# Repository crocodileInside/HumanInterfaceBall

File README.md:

# HumanInterfaceBall
A ball-shaped, BLE enabled human interface device using a **Bosch BNO055** IMU and a **Bosch BME280** environment sensor for mouse input control.  

## Hardware  
Using a RedBearLabs BLE Nano v2 (**nRF52832**) as MCU and for BLE communication.

## Software  
Written in Arduino, see Arduino folder

### Installation instructions  
In order to setup the required toolchain, follow these instructions:

1. Download and install [Arduino IDE](https://www.arduino.cc/en/Main/Software) >=1.6.12 (tested with 1.6.12)  
2. Install `arduino-nRF5` as described here: https://github.com/sandeepmistry/arduino-nRF5
3. Copy the contents of the `Arduino/libraries/` folder to your Arduino library folder (most likely at `Documents/Arduino/libraries`)
4. The default pin function mapping of our board in Arduino doesn't work with our PCB, so you need to replace your `variant.h` with the one provided in `Arduino/variant.h`  
The original variant.h is found at `C:\Users\<Username>\AppData\Local\Arduino15\packages\sandeepmistry\hardware\nRF5\0.4.0\variants\RedBear_BLENano2`
5. Plug in the DAPLink
6. Install the [mbed Serial Driver](https://os.mbed.com/handbook/Windows-serial-configuration)
7. Open the Arduino IDE (or restart, if it was open)
8. Choose *Tools -> Board -> RedBear BLE Nano 2*
9. Choose *Tools -> Softdevice -> S132*
10. Select the correct serial port for the DAPLink at *Tools -> Port* (sometimes displayed as *BBC:microBit*)
11. Choose *Tools -> Programmer -> CMSIS-DAP*
12. **factory new boards only**: Select *Tools -> nRF5 Flash SoftDevice* and wait for completion
13. Compile and flash the software using Arduino (or hit CTRL+U)
14. Finished!

*Created 01/2018 by C. Locher, M. Schuster, S. Oechslein, N. Rieth, T. Windberg*

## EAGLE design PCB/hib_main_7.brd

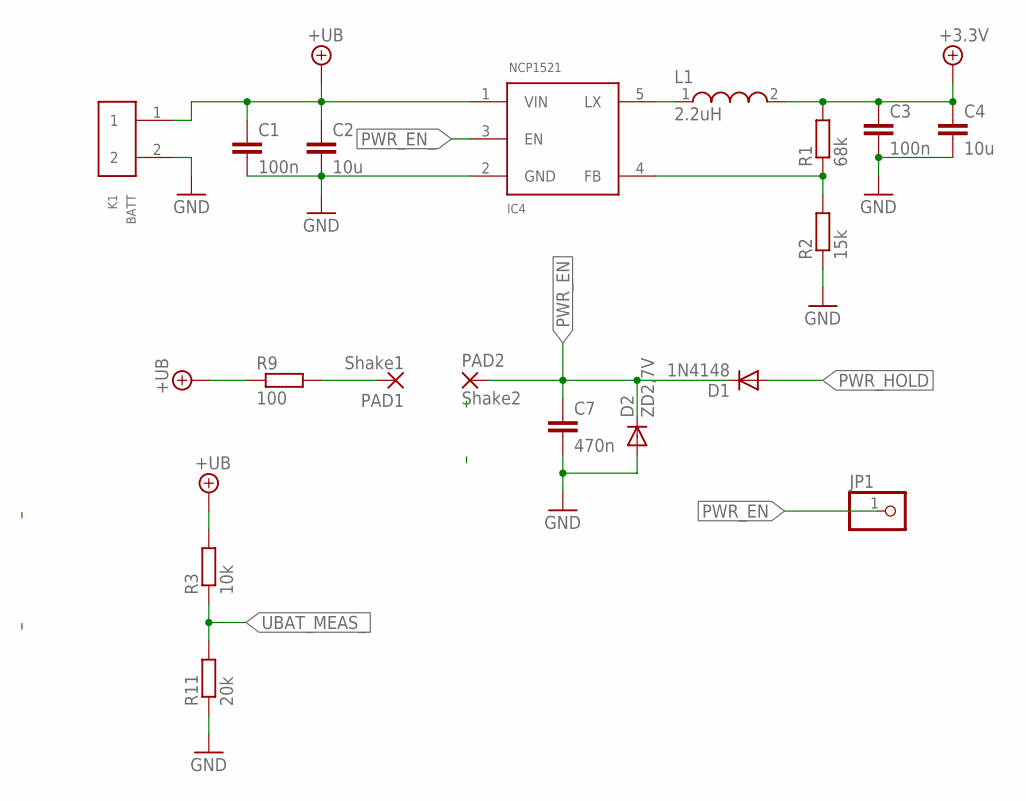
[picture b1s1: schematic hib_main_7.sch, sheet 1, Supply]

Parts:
C1: 100n; C0805K
C2: 10u; C0805K
C3: 100n; C0805M
C4: 10u; C0805M
C7: 470n; C0805M
D1: 1N4148; MINIMELF
D2: ZD2,7V; MINIMELF
IC4: NCP1521; SOT23-5L
JP1: PINHD-1X1; 1X01
K1: BATT; 620102131822
L1: 2.2uH; WE-MPSB_0805(W=4.0)
PAD1: Shake1; SMD1,27-2,54
PAD2: Shake2; SMD1,27-2,54
R1: 68k; R0603
R2: 15k; R0603
R3: 10k; R0603
R9: 100; R0603
R11: 20k; R0603

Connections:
+3,3V: C3.1, C4.1, L1.2, R1.2; also elsewhere on the board
+UB: C1.1, C2.1, IC4.1 (VIN), K1.1, R3.2, R9.1; also elsewhere on the board
GND: C1.2, C2.2, C3.2, C4.2, C7.2, D2.A, IC4.2 (GND), K1.2, R2.1, R11.1; also elsewhere on the board
unnamed: IC4.5 (LX), L1.1
unnamed: IC4.4 (FB), R1.1, R2.2
unnamed: PAD1.1, R9.2
PWR_EN: C7.1, D1.C, D2.C, JP1.1, PAD2.1
PWR_EN_: IC4.3 (EN); also elsewhere on the board
PWR_HOLD: D1.A; also elsewhere on the board
UBAT_MEAS_: R3.1, R11.2; also elsewhere on the board

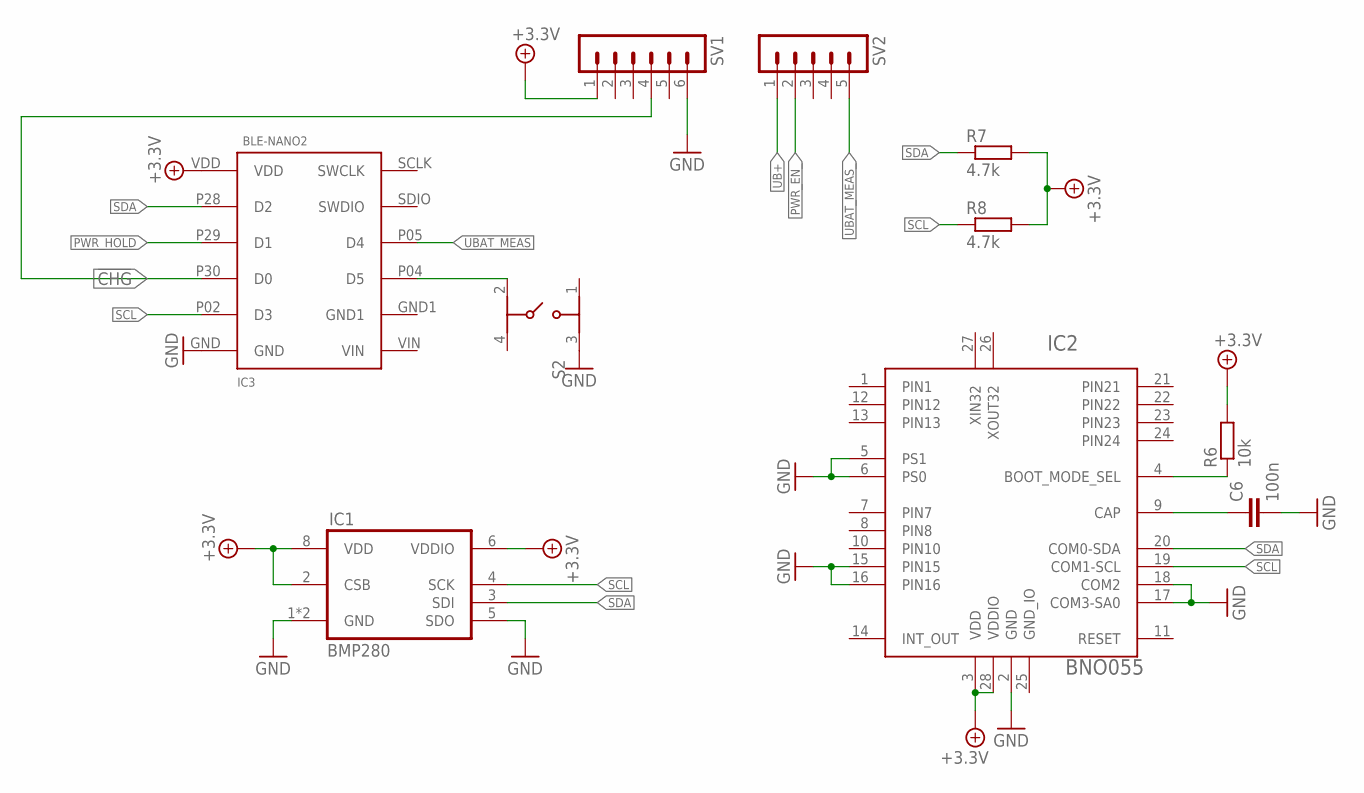
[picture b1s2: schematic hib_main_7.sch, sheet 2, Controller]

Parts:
C6: 100n; C0805M
IC1: BMP280
IC2: BNO055; LGA-28_3.80X5.20/0.5
IC3: BLE-NANO2
R6: 10k; R0805M
R7, R8: 4.7k; R0805M
S2: 434153017835
SV1: MA06-1
SV2: MA05-1

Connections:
!CHG!: IC3.P30 (D0), SV1.4; also elsewhere on the board
+3,3V: IC1.2 (CSB), IC1.6 (VDDIO), IC1.8 (VDD), IC2.3 (VDD), IC2.28 (VDDIO), IC3.VDD, R6.2, R7.2, R8.2, SV1.1; also elsewhere on the board
GND: C6.2, IC1.1 (GND), IC1.5 (SDO), IC1.7 (GND), IC2.2 (GND), IC2.5 (PS1), IC2.6 (PS0), IC2.15 (PIN15), IC2.16 (PIN16), IC2.17 (COM3-SA0), IC2.18 (COM2), IC3.GND, S2.3 (2), SV1.6; also elsewhere on the board
GND_IO: IC2.25 (GND_IO)
unnamed: C6.1, IC2.9 (CAP)
unnamed: IC2.4 (BOOT_MODE_SEL), R6.1
PWR_EN_: SV2.2; also elsewhere on the board
PWR_HOLD: IC3.P29 (D1); also elsewhere on the board
RESET: IC3.P04 (D5), S2.2 (3)
SCL: IC1.4 (SCK), IC2.19 (COM1-SCL), IC3.P02 (D3), R8.1
SDA: IC1.3 (SDI), IC2.20 (COM0-SDA), IC3.P28 (D2), R7.1
UB+: SV2.1
UBAT_MEAS: IC3.P05 (D4)
UBAT_MEAS_: SV2.5; also elsewhere on the board

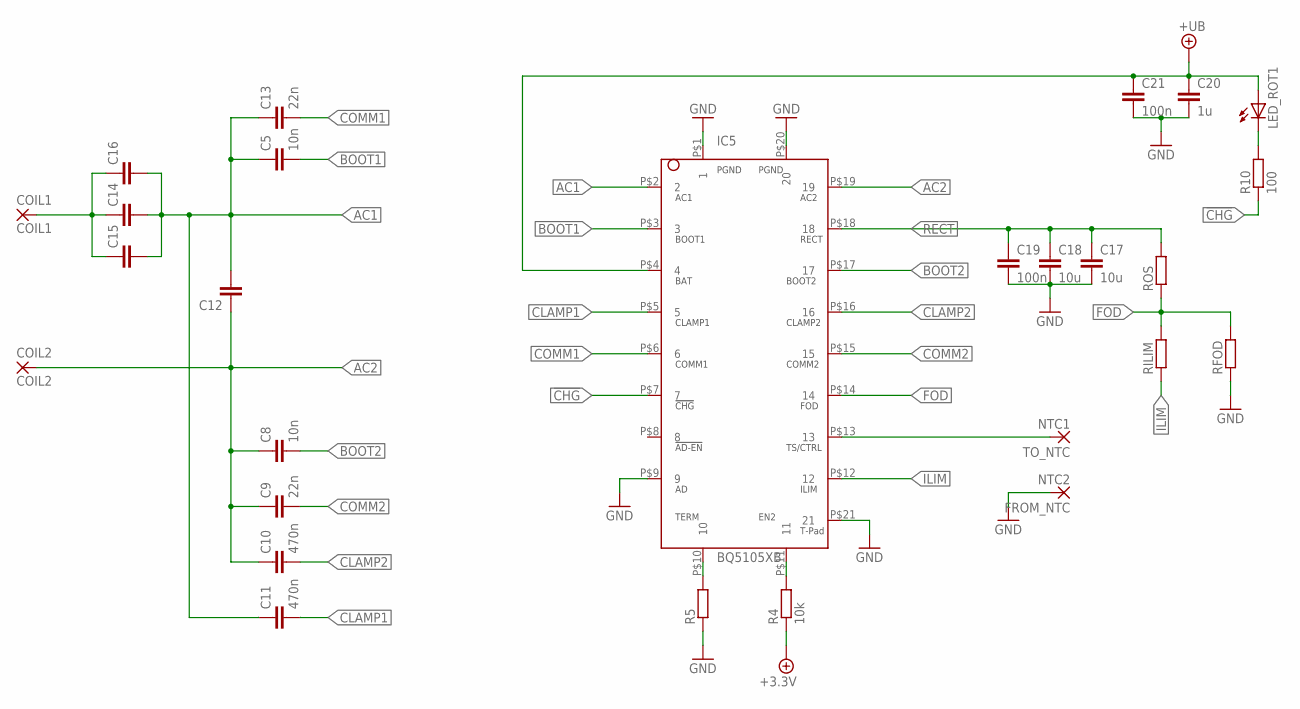
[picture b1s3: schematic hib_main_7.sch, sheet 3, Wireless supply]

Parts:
C5, C8: 10n; C0603K
C9, C13: 22n; C0603K
C10, C11: 470n; C0603K
C12, C14, C15, C16: C-EUC0603K; C0603K
C17, C18: 10u; C0603K
C19, C21: 100n; C0603K
C20: 1u; C0603K
COIL1: COIL1; SMD1,27-2,54
COIL2: COIL2; SMD1,27-2,54
FROM_NTC: NTC2; SMD1,27-2,54
IC5: BQ5105XB; VQFN_BQ5105B
LED_ROT1: LEDCHIP-LED0603; CHIP-LED0603
R4: 10k; R0805
R5: R-EU_R0603; R0603
R10: 100; R0603
RFOD: R-EU_R0805; R0805
RILIM: R-EU_R0805; R0805
ROS: R-EU_R0805; R0805
TO_NTC: NTC1; SMD1,27-2,54

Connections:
!CHG!: IC5.P$7 (7), R10.1; also elsewhere on the board
+3,3V: R4.1; also elsewhere on the board
+UB: C20.1, C21.1, IC5.P$4 (4), LED_ROT1.A; also elsewhere on the board
AC1: C5.1, C11.1, C12.2, C13.1, C14.2, C15.2, C16.2, IC5.P$2 (2)
AC2: C8.1, C9.1, C10.1, C12.1, COIL2.1, IC5.P$19 (19)
BOOT1: C5.2, IC5.P$3 (3)
BOOT2: C8.2, IC5.P$17 (17)
CLAMP1: C11.2, IC5.P$5 (5)
CLAMP2: C10.2, IC5.P$16 (16)
COMM1: C13.2, IC5.P$6 (6)
COMM2: C9.2, IC5.P$15 (15)
FOD: IC5.P$14 (14), RFOD.2, RILIM.2, ROS.1
GND: C17.2, C18.2, C19.2, C20.2, C21.2, FROM_NTC.1, IC5.P$1 (1), IC5.P$9 (9), IC5.P$20 (20), IC5.P$21 (21), R5.1, RFOD.1; also elsewhere on the board
ILIM: IC5.P$12 (12), RILIM.1
unnamed: C14.1, C15.1, C16.1, COIL1.1
unnamed: IC5.P$10 (10), R5.2
unnamed: IC5.P$11 (11), R4.2
unnamed: LED_ROT1.C, R10.2
RECT: C17.1, C18.1, C19.1, IC5.P$18 (18), ROS.2
TS/CTRL: IC5.P$13 (13), TO_NTC.1

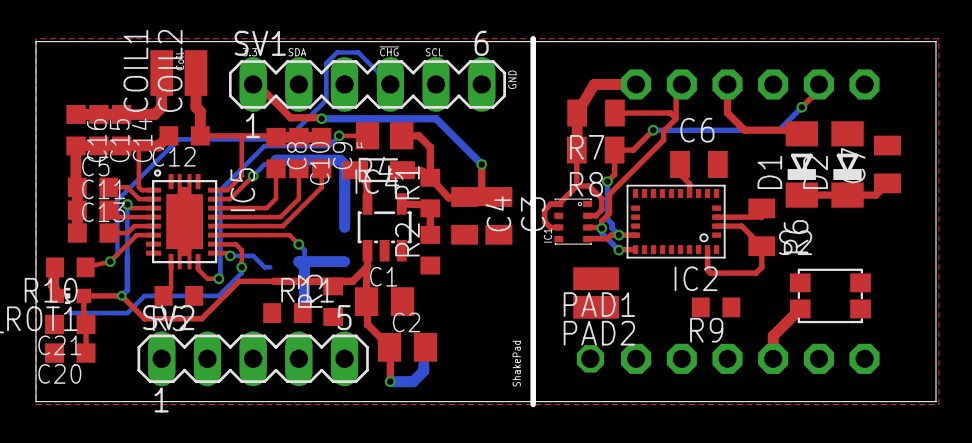
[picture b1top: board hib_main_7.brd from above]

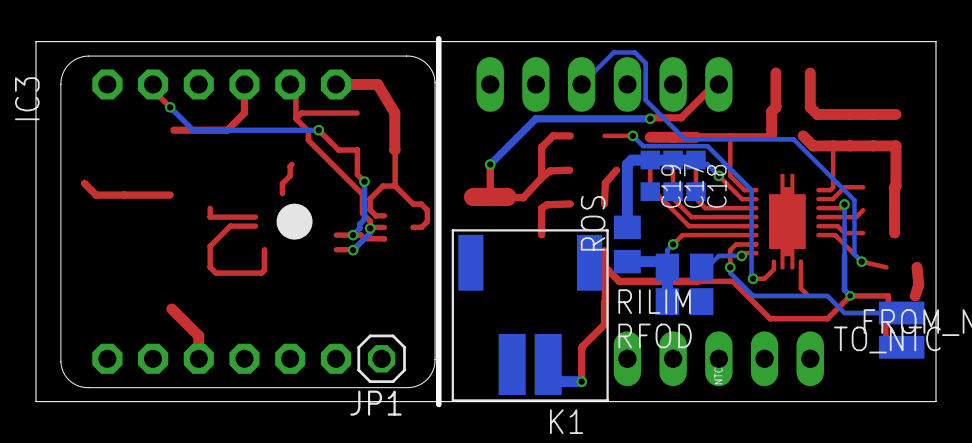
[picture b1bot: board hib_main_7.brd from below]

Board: 2 copper layers, 49.7 x 20.3 mm, 55 parts (11 on the bottom side), 32 nets.

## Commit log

2017-11-23 initial commit, including NRF HID example project
2017-11-23 added ble_app_uart
2017-11-23 removed bullshit
2017-11-23 added example project HIB_fw
2017-11-23 added i2c example
2017-11-23 added twi_sensor
2018-01-17 added arduino version
2018-01-17 uodated values
2018-01-20 Linksklick halten Rechtsklick
2018-01-20 Add scroll function
    condition is a acceleration in y direction or a acceleration in z direction
2018-01-20 added README.md added Datasheets added variant.h
2018-01-23 added Datasheets/BST-BME280_DS001-12.pdf, README.DE.md

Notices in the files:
parts and their libraries:
EagleLibrary_Wuerth_Elektronik_eiSos_rev: Copyright: Würth Elektronik
